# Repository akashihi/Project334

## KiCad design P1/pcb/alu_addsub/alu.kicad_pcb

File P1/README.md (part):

# P1 - Processor One 

Simple 8-bit stack based CPU built with standard logic ICs.

## Contents

- [Project organization](#project-organization)
- [Architecture](#architecture)
- [Toolchain](#toolchain)
- [Logical design]
- [Schematics and PCB]
- [Authors]
- [License]

## Project Organization

* `benchmark` - Host system benchmark code. Implements several matrix operation on 8-bit
unsigned integers.
* `docs` - More detailed documentation on the CPU design and Instruction Set Architecture.
* `prgs` - Programs written for P1 CPU using P1 mnemonics
* `tb` - Test vector generators for ALU and branching unit. 
* `tests` - Test programs in P1 mnemonics that execute every single possible opcode in a predictable manner
* `tooling` - Mnemonics translation tool `p1asm` and CPU emulator `p1emu`

CPU logical design is done in [Logisim Evolution](https://github.com/logisim-evolution/logisim-evolution), the main circuit is 
stored in `P1.circ` file. 

CPU physical design is done in [KiCad](https://www.kicad.org/)

Tooling is written in [Rust](https://rustup.rs/)

## Architecture

P1 is a simple 8-bit, stack based CPU with 8-bit address and data buses. The main characteristic of it as it is a 
stack-based CPU, meaning that all operations are executed on a hardware stack, not on addressable registers.

CPU provides four items stack with registers `X`,`Y`,`Z` and `T`, plus a "previous X value" register `X0`. 
All operations are applied to the values of registers `X` and `Y` and operations results are stored back to register `X`. 
CPU provides wide set of stack specific operations.

For an intermediate data storage CPU provides 15 addressable registers, which can be used as a temporary data storage. 
Those registers can not be used in any other operation, except reading or updating their value. However, those 
registers could be used with branching instructions, procedure calls or data accesses as the source of address, 
thus allowing indirect operations. Some of those registers will automatically increase of decrease their values upon 
indirect call, thus allowing automatic sequential reads/write of memory.

Speaking of memory, CPU support 256 bytes of RAM **and** 256 bytes of program ROM. Program memory and data memory are in 
different address spaces, however they share the same address and data buses.

More details on the CPU instructions and behaviour details can be obtained from the [Instruction Set Architecture documentation](/docs/ISA.md).

## Toolchain

What toolchain? There is no real toolchain, but rather a couple of tools that help you write and debug programs for P1 cpu.

### p1asm

Located under `tooling\p1asm` is a Rust tool to convert a program written in P1 autocode to the executable binary. `p1asm` tool
 accepts a text source file and generates a binary file, replacing source file's extension with `p1b`. Example:

````shell
>cargo run hello_world.p1s
Converting hello_world.p1s input file to "hello_world.p1b" output binary
LUP 248 -> 01001111
PUP 248 -> 01011000
WVR R15 -> 11011111
LUP 72 -> 01000100
PUP 72 -> 01011000
ST R15 -> 10011111
LUP 105 -> 01000110
PUP 105 -> 01011001
ST R15 -> 10011111
SET 32 -> 00100000
ST R15 -> 10011111
LUP 116 -> 01000111
PUP 116 -> 01010100
ST R15 -> 10011111
LUP 104 -> 01000110
PUP 104 -> 01011000
ST R15 -> 10011111
LUP 101 -> 01000110
PUP 101 -> 01010101
ST R15 -> 10011111
LUP 114 -> 01000111
PUP 114 -> 01010010
ST R15 -> 10011111
LUP 101 -> 01000110
PUP 101 -> 01010101
ST R15 -> 10011111                                                                                                                                                                                                                                                                                                          
````

`p1asm` expects an input file with a single opcode per line. For the register addressing opcodes, like `ST` please use an `R` prefix: `ST R15`.
For the register addressing opcodes, that operate on the `Y` register, please provide the register name directly: `LD Y`.

Assembly tool automatically checks that your program contains not more than 256 program steps and will fail on program memory overflow. 
Please pay attention, that you should use `SET` opcode instead of the `LUP/PUP` and `load immediate`. Assembly tool will automatically
convert those set call to either pair of `LUP/PUP` or to the short load of the immediate.

Unfortunately otherwise the tool is pretty limited and doesn't provide neither linking nor other automation. It is recommended to use supplied
`prgs\template.p1s` for tracking the addresses and track the content of the stack manually, like it is done in `tests\test_alu_ops.p1s`.

### p1emu

Second tool is located under `tooling\p1emu` and emulates the instruction set architecture of the P1 CPU. For the more precise cycle-perfect simulation
one can use the [logical design simulation](#logical-design) with logisim.

However, neither hardware implementation nor logisim provide convenient debug interface and ease of use. On the other hand the `p1emu` tool 
provides you with a simple way to run a P1 software on the host system and dumps the CPU state on each opcode processed. Additionally, 
it allows you to load pre-saved RAM or store it to the file at the end of the execution. The `p1emu` tool treats the NOP opcode as the execution
completion marker, unlike logisim model (and, obviously, hardware), which just skips to the next opcode. Example:

````shell
>cargo run hello_world.p1b -w hello_world.ram
Loading program code from hello_world.p1b
Loaded 26 bytes
PC: 000, X0: 000, X: 000, Y: 000, Z: 000, T: 000, S0: 000, S1: 000, S2: 000, S3: 000
R1: 000 R2: 000 R3: 000 R4: 000 R5: 000 R6: 000 R7: 000 R8: 000 R9: 000 R10: 000 R11: 000 R12: 000 R13: 000 R14: 000 R15: 000 
Output: 000 000 000 000 000 000 000 000 000 000  : 
Opcode: 01001111, Instruction: LUP 240
PC: 001, X0: 000, X: 240, Y: 000, Z: 000, T: 000, S0: 000, S1: 000, S2: 000, S3: 000
R1: 000 R2: 000 R3: 000 R4: 000 R5: 000 R6: 000 R7: 000 R8: 000 R9: 000 R10: 000 R11: 000 R12: 000 R13: 000 R14: 000 R15: 000 
Output: 000 000 000 000 000 000 000 000 000 000  : 
Opcode: 01011000, Instruction: PUP 8
PC: 002, X0: 000, X: 248, Y: 000, Z: 000, T: 000, S0: 000, S1: 000, S2: 000, S3: 000
R1: 000 R2: 000 R3: 000 R4: 000 R5: 000 R6: 000 R7: 000 R8: 000 R9: 000 R10: 000 R11: 000 R12: 000 R13: 000 R14: 000 R15: 000 
Output: 000 000 000 000 000 000 000 000 000 000  : 
Opcode: 11011111, Instruction: WVR 15
PC: 003, X0: 000, X: 248, Y: 000, Z: 000, T: 000, S0: 000, S1: 000, S2: 000, S3: 000
R1: 000 R2: 000 R3: 000 R4: 000 R5: 000 R6: 000 R7: 000 R8: 000 R9: 000 R10: 000 R11: 000 R12: 000 R13: 000 R14: 000 R15: 248 
Output: 000 000 000 000 000 000 000 000 000 000  : 
Opcode: 01000100, Instruction: LUP 64
PC: 004, X0: 000, X: 072, Y: 000, Z: 000, T: 000, S0: 000, S1: 000, S2: 000, S3: 000
R1: 000 R2: 000 R3: 000 R4: 000 R5: 000 R6: 000 R7: 000 R8: 000 R9: 000 R10: 000 R11: 000 R12: 000 R13: 000 R14: 000 R15: 248 
Output: 000 000 000 000 000 000 000 000 000 000  : 
Opcode: 01011000, Instruction: PUP 8
PC: 005, X0: 000, X: 072, Y: 000, Z: 000, T: 000, S0: 000, S1: 000, S2: 000, S3: 000
R1: 000 R2: 000 R3: 000 R4: 000 R5: 000 R6: 000 R7: 000 R8: 000 R9: 000 R10: 000 R11: 000 R12: 000 R13: 000 R14: 000 R15: 248 
Output: 000 000 000 000 000 000 000 000 000 000  : 
Opcode: 10011111, Instruction: ST 15
PC: 006, X0: 000, X: 072, Y: 000, Z: 000, T: 000, S0: 000, S1: 000, S2: 000, S3: 000
R1: 000 R2: 000 R3: 000 R4: 000 R5: 000 R6: 000 R7: 000 R8: 000 R9: 000 R10: 000 R11: 000 R12: 000 R13: 000 R14: 000 R15: 249 
Output: 000 000 072 000 000 000 000 000 000 000  : 
Opcode: 01000110, Instruction: LUP 96
PC: 007, X0: 000, X: 104, Y: 000, Z: 000, T: 000, S0: 000, S1: 000, S2: 000, S3: 000
R1: 000 R2: 000 R3: 000 R4: 000 R5: 000 R6: 000 R7: 000 R8: 000 R9: 000 R10: 000 R11: 000 R12: 000 R13: 000 R14: 000 R15: 249 
Output: 000 000 072 000 000 000 000 000 000 000  : 
Opcode: 01011001, Instruction: PUP 9
PC: 008, X0: 000, X: 105, Y: 000, Z: 000, T: 000, S0: 000, S1: 000, S2: 000, S3: 000
R1: 000 R2: 000 R3: 000 R4: 000 R5: 000 R6: 000 R7: 000 R8: 000 R9: 000 R10: 000 R11: 000 R12: 000 R13: 000 R14: 000 R15: 249 
Output: 000 000 072 000 000 000 000 000 000 000  : 
Opcode: 10011111, Instruction: ST 15
PC: 009, X0: 000, X: 105, Y: 000, Z: 000, T: 000, S0: 000, S1: 000, S2: 000, S3: 000
R1: 000 R2: 000 R3: 000 R4: 000 R5: 000 R6: 000 R7: 000 R8: 000 R9: 000 R10: 000 R11: 000 R12: 000 R13: 000 R14: 000 R15: 250 
Output: 000 000 072 105 000 000 000 000 000 000  : 
Opcode: 00100000, Instruction: Immediate: 32
PC: 010, X0: 000, X: 032, Y: 000, Z: 000, T: 000, S0: 000, S1: 000, S2: 000, S3: 000
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
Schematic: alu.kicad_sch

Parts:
C1, C2, C3, C4, C5, C6, C7, C8, C9, C10, C13, C14, C23, C24, C25, C26: 100n; C_1206_3216Metric
J1: 650473-5; TE_650473-5; PARTREV S
U1, U4, U6, U9, U14, U15: 74HC86; TSSOP-14_4.4x5mm_P0.65mm
U2, U5, U7: 74LS08; TSSOP-14_4.4x5mm_P0.65mm
U3, U30: 74LS32; TSSOP-14_4.4x5mm_P0.65mm
U8: 74LS32
U10: 74LS08
U13: 74LS541; SOIC-20W_7.5x12.8mm_P1.27mm
U29: 74HC238; TSSOP-16_4.4x5mm_P0.65mm
U31: 74LS621; SOIC-20W_7.5x12.8mm_P1.27mm

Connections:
+5V: C1.1, C2.1, C3.1, C4.1, C5.1, C6.1, C7.1, C8.1, C9.1, C10.1, C13.1, C14.1, C23.1, C24.1, C25.1, C26.1, J1.A32, J1.C29, J1.C32, U1.14 (VCC), U2.14 (VCC), U3.14 (VCC), U4.14 (VCC), U5.14 (VCC), U6.14 (VCC), U7.14 (VCC), U8.14 (VCC), U9.14 (VCC), U10.14 (VCC), U13.20 (VCC), U14.14 (VCC), U15.14 (VCC), U29.16 (VCC), U30.14 (VCC), U31.19 (~GBA), U31.20 (VCC)
/RESULT0: U1.3, U31.2 (A0)
/RESULT1: U1.6, U31.3 (A1)
/RESULT2: U1.8, U31.4 (A2)
/RESULT3: U1.11, U31.5 (A3)
/RESULT4: U6.3, U31.6 (A4)
/RESULT5: U6.6, U31.7 (A5)
/RESULT6: U6.8, U31.8 (A6)
/RESULT7: U6.11, U31.9 (A7)
/T0: U2.5, U4.2, U15.3
/T1: U2.13, U4.5, U15.6
/T2: U4.10, U5.5, U15.8
/T3: U4.13, U5.13, U15.11
/T4: U7.5, U9.13, U14.3
/T5: U7.13, U9.10, U14.6
/T6: U9.5, U10.5, U14.8
/T7: U9.2, U14.11
/X_IN0: J1.A19, U31.18 (B0)
/X_IN1: J1.A20, U31.17 (B1)
/X_IN2: J1.A21, U31.16 (B2)
/X_IN3: J1.A22, U31.15 (B3)
/X_IN4: J1.A23, U31.14 (B4)
/X_IN5: J1.A24, U31.13 (B5)
/X_IN6: J1.A25, U31.12 (B6)
/X_IN7: J1.A26, U31.11 (B7)
/X_OUT0: U2.4, U4.1, U13.11 (Y7)
/X_OUT1: U2.12, U4.4, U13.12 (Y6)
/X_OUT2: U4.9, U5.4, U13.13 (Y5)
/X_OUT3: U4.12, U5.12, U13.14 (Y4)
/X_OUT4: U7.4, U9.12, U13.15 (Y3)
/X_OUT5: U7.12, U9.9, U13.16 (Y2)
/X_OUT6: U9.4, U10.4, U13.17 (Y1)
/X_OUT7: U9.1, U13.18 (Y0)
/Y_OUT0: J1.A10, U15.1
/Y_OUT1: J1.A11, U15.4
/Y_OUT2: J1.A12, U15.9
/Y_OUT3: J1.A13, U15.12
/Y_OUT4: J1.A14, U14.1
/Y_OUT5: J1.A15, U14.4
/Y_OUT6: J1.A16, U14.9
/Y_OUT7: J1.A17, U14.12
GND: C1.2, C2.2, C3.2, C4.2, C5.2, C6.2, C7.2, C8.2, C9.2, C10.2, C13.2, C14.2, C23.2, C24.2, C25.2, C26.2, J1.A9, J1.A18, J1.A27, J1.B6, J1.B15, J1.B24, J1.C5, J1.C10, J1.C17, J1.C26, J1.C28, J1.C30, U1.7 (GND), U2.7 (GND), U3.7 (GND), U4.7 (GND), U5.7 (GND), U6.7 (GND), U7.7 (GND), U8.7 (GND), U8.12, U8.13, U9.7 (GND), U10.7 (GND), U10.9, U10.10, U10.12, U10.13, U13.1 (G1), U13.10 (GND), U13.19 (G2), U14.7 (GND), U15.7 (GND), U29.4 (~E1), U29.5 (~E2), U29.8 (GND), U30.4, U30.5, U30.7 (GND), U30.9, U30.10, U30.12, U30.13, U31.10 (GND)
unnamed: U1.1, U2.2, U4.3
unnamed: U1.4, U2.10, U4.6
unnamed: U1.5, U2.9, U3.3
unnamed: U1.9, U4.8, U5.2
unnamed: U1.10, U3.6, U5.1
unnamed: U1.12, U4.11, U5.10
unnamed: U1.13, U3.8, U5.9
unnamed: U2.3, U3.1
unnamed: U2.6, U3.2
unnamed: U2.8, U3.4
unnamed: U2.11, U3.5
unnamed: U3.9, U5.3
unnamed: U3.10, U5.6
unnamed: U3.11, U6.2, U7.1
unnamed: U3.12, U5.8
unnamed: U3.13, U5.11
unnamed: U6.1, U7.2, U9.11
unnamed: U6.4, U7.10, U9.8
unnamed: U6.5, U7.9, U8.3
unnamed: U6.12, U9.3
unnamed: U6.13, U8.8
unnamed: U7.3, U8.1
unnamed: U7.6, U8.2
unnamed: U7.8, U8.4
unnamed: U7.11, U8.5
unnamed: U6.10, U8.6, U10.1
unnamed: U6.9, U9.6, U10.2
unnamed: U8.9, U10.3
unnamed: U8.10, U10.6
unnamed: J1.A8, U13.2 (A0)
unnamed: J1.A7, U13.3 (A1)
unnamed: J1.A6, U13.4 (A2)
unnamed: J1.A5, U13.5 (A3)
unnamed: J1.A4, U13.6 (A4)
unnamed: J1.A3, U13.7 (A5)
unnamed: J1.A2, U13.8 (A6)
unnamed: J1.A1, U13.9 (A7)
unnamed: J1.A31, U29.1 (A0)
unnamed: J1.A30, U29.2 (A1)
unnamed: J1.A29, U29.3 (A2)
unnamed: J1.A28, U29.6 (E3)
unnamed: U29.15 (Y0), U30.1
unnamed: U1.2, U2.1, U14.2, U14.5, U14.10, U14.13, U15.2, U15.5, U15.10, U15.13, U29.14 (Y1), U30.2
unnamed: U30.3, U31.1 (GAB)

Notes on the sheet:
Subtractor XORs decoupling
A0/B0 Adder
A7/B7 Adder
4-bit adder decoupling
A1/B1 Adder
2's complement
A5/B5 Adder
A6/B6 Adder
A2/B2 Adder
A3/B3 Adder
A4/B4 Adder

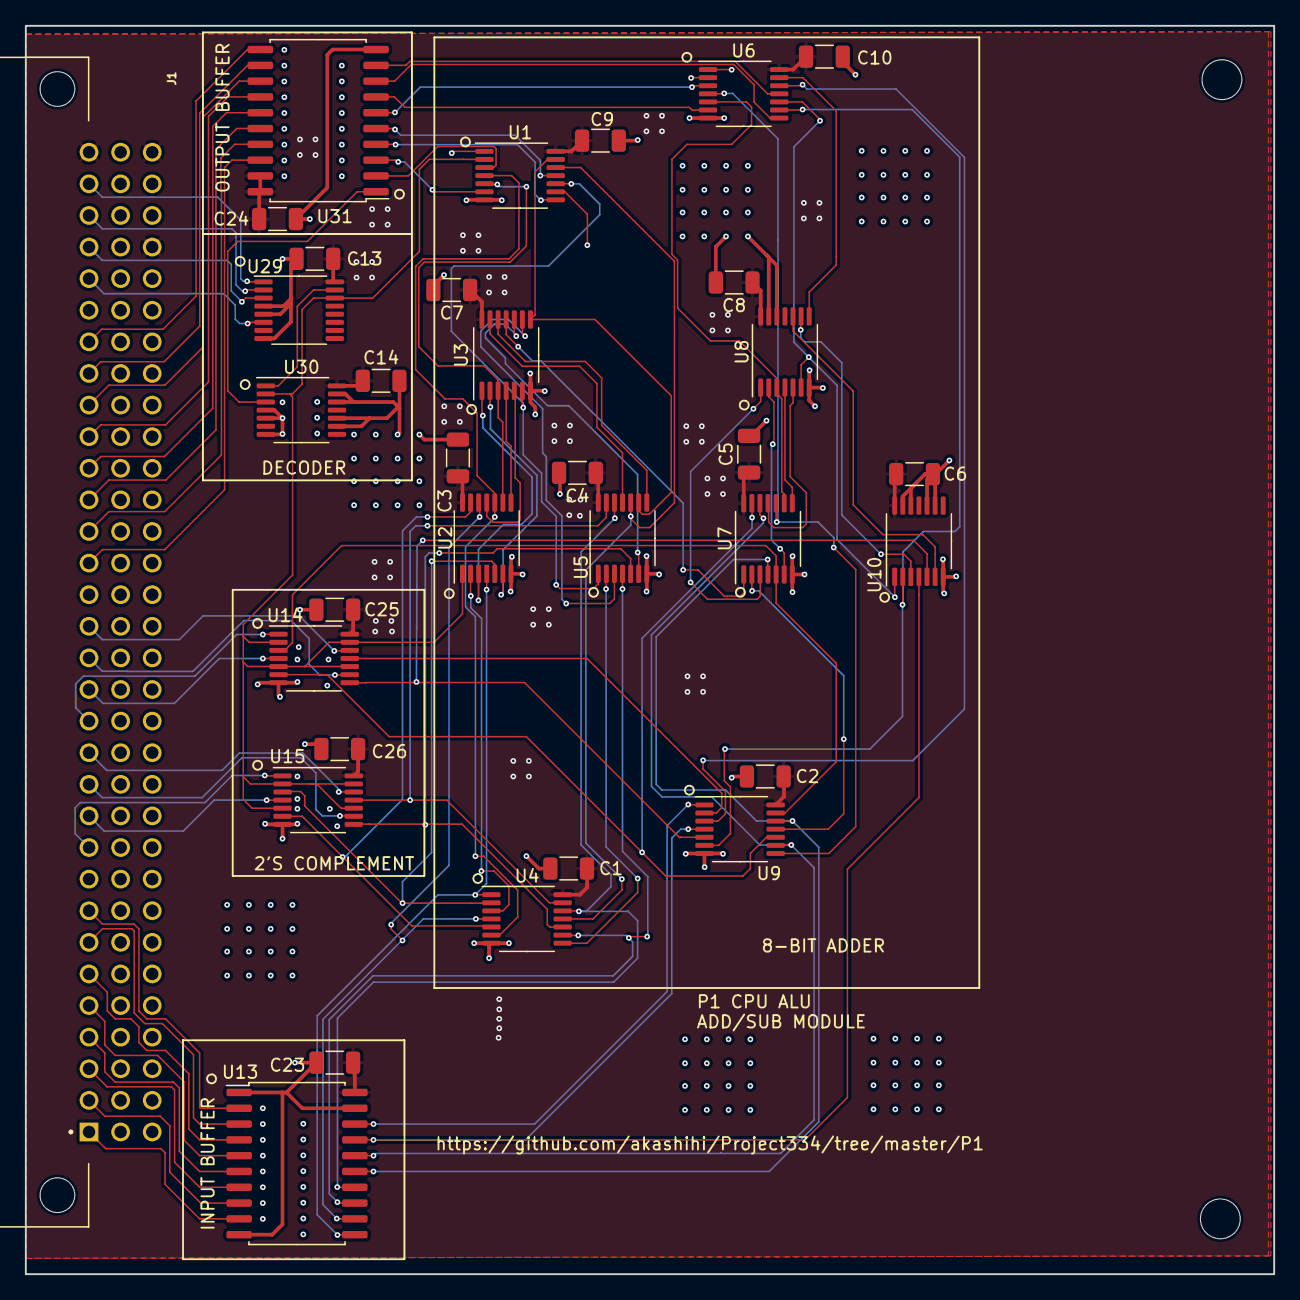
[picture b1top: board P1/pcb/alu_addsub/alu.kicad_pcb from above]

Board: 4 copper layers, 100.3 x 100.3 mm, 33 parts (0 on the bottom side), 86 nets.

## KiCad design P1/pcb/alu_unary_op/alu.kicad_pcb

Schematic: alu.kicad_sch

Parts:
C1, C23, C24, C25, C26, C27, C28, C29, C30: 100n; C_1206_3216Metric
J1: 650473-5; TE_650473-5; PARTREV S
U13: 74LS541; SOIC-20W_7.5x12.8mm_P1.27mm
U23, U24: 74HC04; TSSOP-14_4.4x5mm_P0.65mm
U25, U28: 74LS621; SOIC-20W_7.5x12.8mm_P1.27mm
U26, U27: 74LS157; TSSOP-16_4.4x5mm_P0.65mm
U29: 74HC238; TSSOP-16_4.4x5mm_P0.65mm
U30: 74LS32; TSSOP-14_4.4x5mm_P0.65mm

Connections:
+5V: C1.1, C23.1, C24.1, C25.1, C26.1, C27.1, C28.1, C29.1, C30.1, J1.A32, J1.C29, J1.C32, U13.20 (VCC), U23.14 (VCC), U24.5, U24.9, U24.11, U24.13, U24.14 (VCC), U25.19 (~GBA), U25.20 (VCC), U26.16 (VCC), U27.16 (VCC), U28.19 (~GBA), U28.20 (VCC), U29.16 (VCC), U30.14 (VCC)
/X_IN0: J1.A19, U25.18 (B0), U28.18 (B0)
/X_IN1: J1.A20, U25.17 (B1), U28.17 (B1)
/X_IN2: J1.A21, U25.16 (B2), U28.16 (B2)
/X_IN3: J1.A22, U25.15 (B3), U28.15 (B3)
/X_IN4: J1.A23, U25.14 (B4), U28.14 (B4)
/X_IN5: J1.A24, U25.13 (B5), U28.13 (B5)
/X_IN6: J1.A25, U25.12 (B6), U28.12 (B6)
/X_IN7: J1.A26, U25.11 (B7), U28.11 (B7)
/X_OUT0: U13.11 (Y7), U23.5, U26.6 (I1b)
/X_OUT1: U13.12 (Y6), U23.3, U26.2 (I0a), U26.10 (I1c)
/X_OUT2: U13.13 (Y5), U23.1, U26.5 (I0b), U26.13 (I1d)
/X_OUT3: U13.14 (Y4), U23.9, U26.11 (I0c), U27.3 (I1a)
/X_OUT4: U13.15 (Y3), U23.11, U26.14 (I0d), U27.6 (I1b)
/X_OUT5: U13.16 (Y2), U23.13, U27.2 (I0a), U27.10 (I1c)
/X_OUT6: U13.17 (Y1), U24.3, U27.5 (I0b), U27.13 (I1d)
/X_OUT7: U13.18 (Y0), U24.1, U27.11 (I0c)
GND: C1.2, C23.2, C24.2, C25.2, C26.2, C27.2, C28.2, C29.2, C30.2, J1.A9, J1.A18, J1.A27, J1.B6, J1.B15, J1.B24, J1.C5, J1.C10, J1.C17, J1.C26, J1.C28, J1.C30, U13.1 (G1), U13.10 (GND), U13.19 (G2), U23.7 (GND), U24.7 (GND), U25.10 (GND), U26.3 (I1a), U26.8 (GND), U26.15 (E), U27.8 (GND), U27.14 (I0d), U27.15 (E), U28.10 (GND), U29.4 (~E1), U29.5 (~E2), U29.8 (GND), U30.1, U30.2, U30.7 (GND), U30.9, U30.10, U30.12, U30.13
unnamed: J1.A8, U13.2 (A0)
unnamed: J1.A7, U13.3 (A1)
unnamed: J1.A6, U13.4 (A2)
unnamed: J1.A5, U13.5 (A3)
unnamed: J1.A4, U13.6 (A4)
unnamed: J1.A3, U13.7 (A5)
unnamed: J1.A2, U13.8 (A6)
unnamed: J1.A1, U13.9 (A7)
unnamed: U23.6, U25.2 (A0)
unnamed: U23.4, U25.3 (A1)
unnamed: U23.2, U25.4 (A2)
unnamed: U23.8, U25.5 (A3)
unnamed: U23.10, U25.6 (A4)
unnamed: U23.12, U25.7 (A5)
unnamed: U24.4, U25.8 (A6)
unnamed: U24.2, U25.9 (A7)
unnamed: U25.1 (GAB), U29.10 (Y5)
unnamed: U26.1 (S), U27.1 (S), U29.13 (Y2), U30.4
unnamed: U26.4 (Za), U28.2 (A0)
unnamed: U26.7 (Zb), U28.3 (A1)
unnamed: U26.9 (Zc), U28.4 (A2)
unnamed: U26.12 (Zd), U28.5 (A3)
unnamed: U27.4 (Za), U28.6 (A4)
unnamed: U27.7 (Zb), U28.7 (A5)
unnamed: U27.9 (Zc), U28.8 (A6)
unnamed: U27.12 (Zd), U28.9 (A7)
unnamed: U28.1 (GAB), U30.6
unnamed: J1.A31, U29.1 (A0)
unnamed: J1.A30, U29.2 (A1)
unnamed: J1.A29, U29.3 (A2)
unnamed: J1.A28, U29.6 (E3)
unnamed: U29.12 (Y3), U30.5

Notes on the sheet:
L/R SHIFT OP
NOT OP

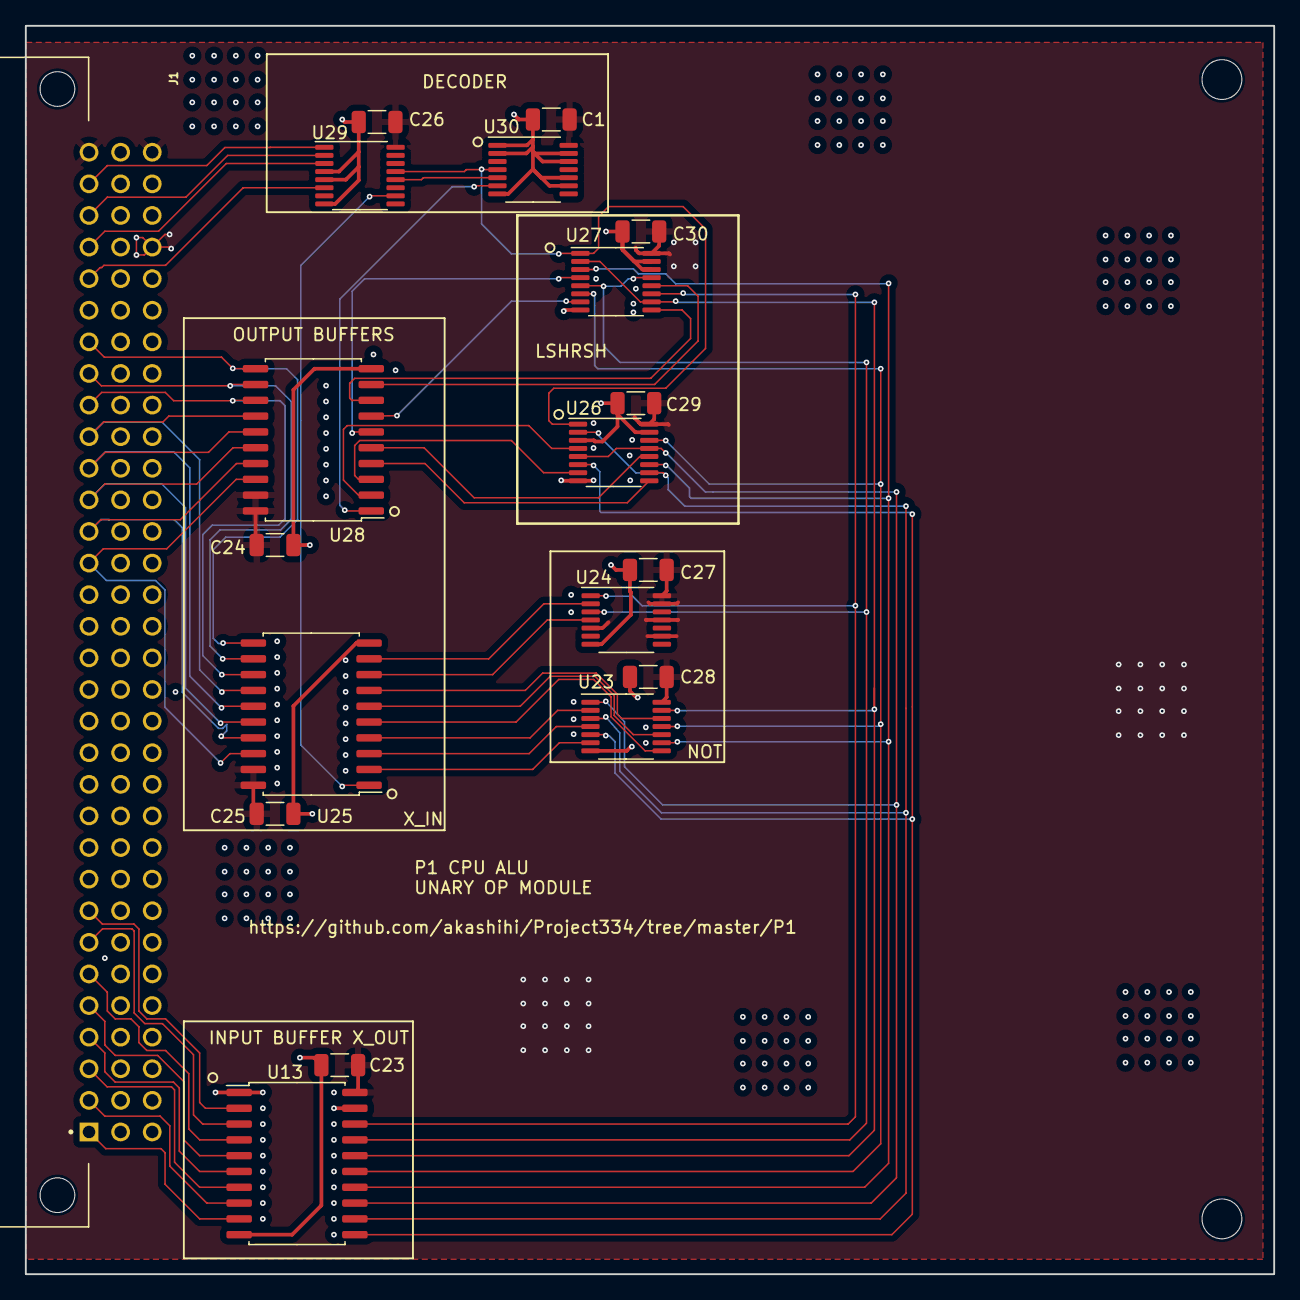
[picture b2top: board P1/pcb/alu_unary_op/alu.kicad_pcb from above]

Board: 4 copper layers, 100.3 x 100.3 mm, 19 parts (0 on the bottom side), 50 nets.

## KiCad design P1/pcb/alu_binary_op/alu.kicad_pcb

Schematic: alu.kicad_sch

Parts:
C13, C14, C15, C23, C24, C25, C26, C27, C28, C29, C30: 100n; C_1206_3216Metric
J1: 650473-5; TE_650473-5; PARTREV S
U13: 74LS541; SOIC-20W_7.5x12.8mm_P1.27mm
U14, U15: 74HC86; TSSOP-14_4.4x5mm_P0.65mm
U16, U19, U22: 74LS621; SOIC-20W_7.5x12.8mm_P1.27mm
U17, U18: 74LS08; TSSOP-14_4.4x5mm_P0.65mm
U20, U21: 74LS32; TSSOP-14_4.4x5mm_P0.65mm
U29: 74HC238; TSSOP-16_4.4x5mm_P0.65mm

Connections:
+5V: C13.1, C14.1, C15.1, C23.1, C24.1, C25.1, C26.1, C27.1, C28.1, C29.1, C30.1, J1.A32, J1.C29, J1.C32, U13.20 (VCC), U14.14 (VCC), U15.14 (VCC), U16.19 (~GBA), U16.20 (VCC), U17.14 (VCC), U18.14 (VCC), U19.19 (~GBA), U19.20 (VCC), U20.14 (VCC), U21.14 (VCC), U22.19 (~GBA), U22.20 (VCC), U29.16 (VCC)
/X_IN0: J1.A19, U16.18 (B0), U19.18 (B0), U22.18 (B0)
/X_IN1: J1.A20, U16.17 (B1), U19.17 (B1), U22.17 (B1)
/X_IN2: J1.A21, U16.16 (B2), U19.16 (B2), U22.16 (B2)
/X_IN3: J1.A22, U16.15 (B3), U19.15 (B3), U22.15 (B3)
/X_IN4: J1.A23, U16.14 (B4), U19.14 (B4), U22.14 (B4)
/X_IN5: J1.A24, U16.13 (B5), U19.13 (B5), U22.13 (B5)
/X_IN6: J1.A25, U16.12 (B6), U19.12 (B6), U22.12 (B6)
/X_IN7: J1.A26, U16.11 (B7), U19.11 (B7), U22.11 (B7)
/X_OUT0: U13.11 (Y7), U14.4, U17.5, U20.5
/X_OUT1: U13.12 (Y6), U14.1, U17.2, U20.2
/X_OUT2: U13.13 (Y5), U14.9, U17.10, U20.10
/X_OUT3: U13.14 (Y4), U14.12, U17.13, U20.13
/X_OUT4: U13.15 (Y3), U15.4, U18.5, U21.5
/X_OUT5: U13.16 (Y2), U15.1, U18.2, U21.2
/X_OUT6: U13.17 (Y1), U15.9, U18.10, U21.10
/X_OUT7: U13.18 (Y0), U15.12, U18.13, U21.13
/Y_OUT0: J1.A10, U14.5, U17.4, U20.4
/Y_OUT1: J1.A11, U14.2, U17.1, U20.1
/Y_OUT2: J1.A12, U14.10, U17.9, U20.9
/Y_OUT3: J1.A13, U14.13, U17.12, U20.12
/Y_OUT4: J1.A14, U15.5, U18.4, U21.4
/Y_OUT5: J1.A15, U15.2, U18.1, U21.1
/Y_OUT6: J1.A16, U15.10, U18.9, U21.9
/Y_OUT7: J1.A17, U15.13, U18.12, U21.12
GND: C13.2, C14.2, C15.2, C23.2, C24.2, C25.2, C26.2, C27.2, C28.2, C29.2, C30.2, J1.A9, J1.A18, J1.A27, J1.B6, J1.B15, J1.B24, J1.C5, J1.C10, J1.C17, J1.C26, J1.C28, J1.C30, U13.1 (G1), U13.10 (GND), U13.19 (G2), U14.7 (GND), U15.7 (GND), U16.10 (GND), U17.7 (GND), U18.7 (GND), U19.10 (GND), U20.7 (GND), U21.7 (GND), U22.10 (GND), U29.4 (~E1), U29.5 (~E2), U29.8 (GND)
unnamed: J1.A8, U13.2 (A0)
unnamed: J1.A7, U13.3 (A1)
unnamed: J1.A6, U13.4 (A2)
unnamed: J1.A5, U13.5 (A3)
unnamed: J1.A4, U13.6 (A4)
unnamed: J1.A3, U13.7 (A5)
unnamed: J1.A2, U13.8 (A6)
unnamed: J1.A1, U13.9 (A7)
unnamed: U14.6, U16.2 (A0)
unnamed: U14.3, U16.3 (A1)
unnamed: U14.8, U16.4 (A2)
unnamed: U14.11, U16.5 (A3)
unnamed: U15.6, U16.6 (A4)
unnamed: U15.3, U16.7 (A5)
unnamed: U15.8, U16.8 (A6)
unnamed: U15.11, U16.9 (A7)
unnamed: U16.1 (GAB), U29.11 (Y4)
unnamed: U17.6, U19.2 (A0)
unnamed: U17.3, U19.3 (A1)
unnamed: U17.8, U19.4 (A2)
unnamed: U17.11, U19.5 (A3)
unnamed: U18.6, U19.6 (A4)
unnamed: U18.3, U19.7 (A5)
unnamed: U18.8, U19.8 (A6)
unnamed: U18.11, U19.9 (A7)
unnamed: U19.1 (GAB), U29.9 (Y6)
unnamed: U20.6, U22.2 (A0)
unnamed: U20.3, U22.3 (A1)
unnamed: U20.8, U22.4 (A2)
unnamed: U20.11, U22.5 (A3)
unnamed: U21.6, U22.6 (A4)
unnamed: U21.3, U22.7 (A5)
unnamed: U21.8, U22.8 (A6)
unnamed: U21.11, U22.9 (A7)
unnamed: U22.1 (GAB), U29.7 (Y7)
unnamed: J1.A31, U29.1 (A0)
unnamed: J1.A30, U29.2 (A1)
unnamed: J1.A29, U29.3 (A2)
unnamed: J1.A28, U29.6 (E3)

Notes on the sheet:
OR OP
XOR OP
AND OP

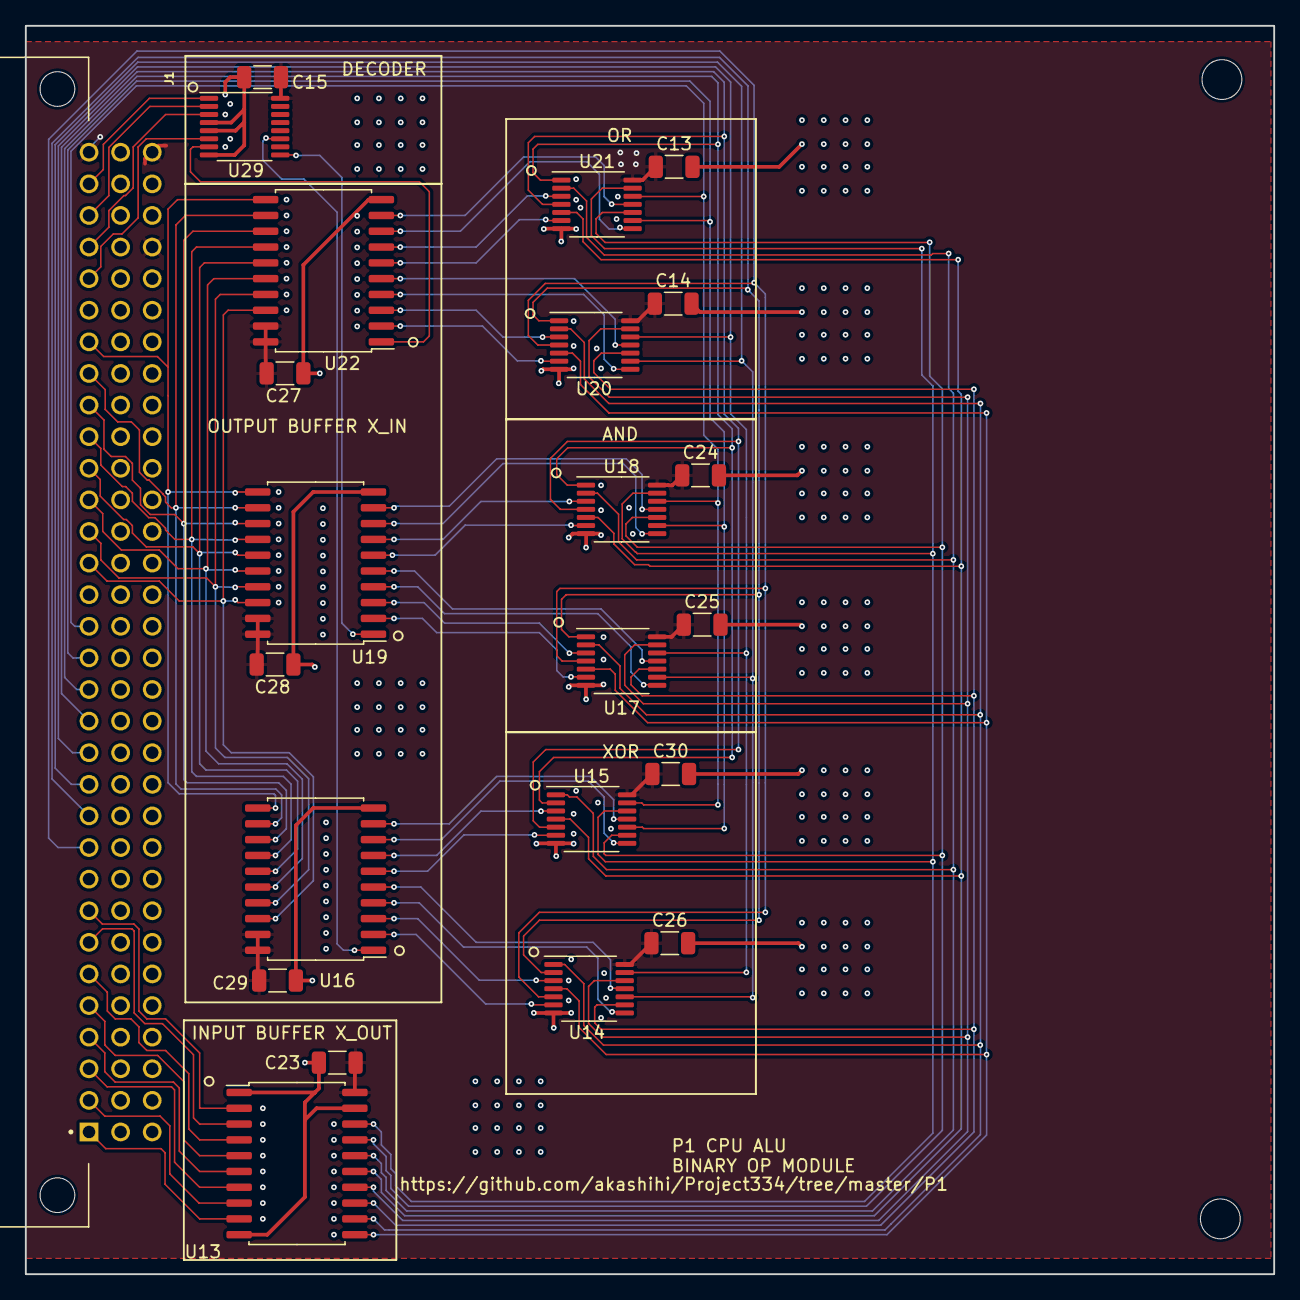
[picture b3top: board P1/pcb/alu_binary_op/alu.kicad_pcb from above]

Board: 4 copper layers, 100.3 x 100.3 mm, 23 parts (0 on the bottom side), 65 nets.

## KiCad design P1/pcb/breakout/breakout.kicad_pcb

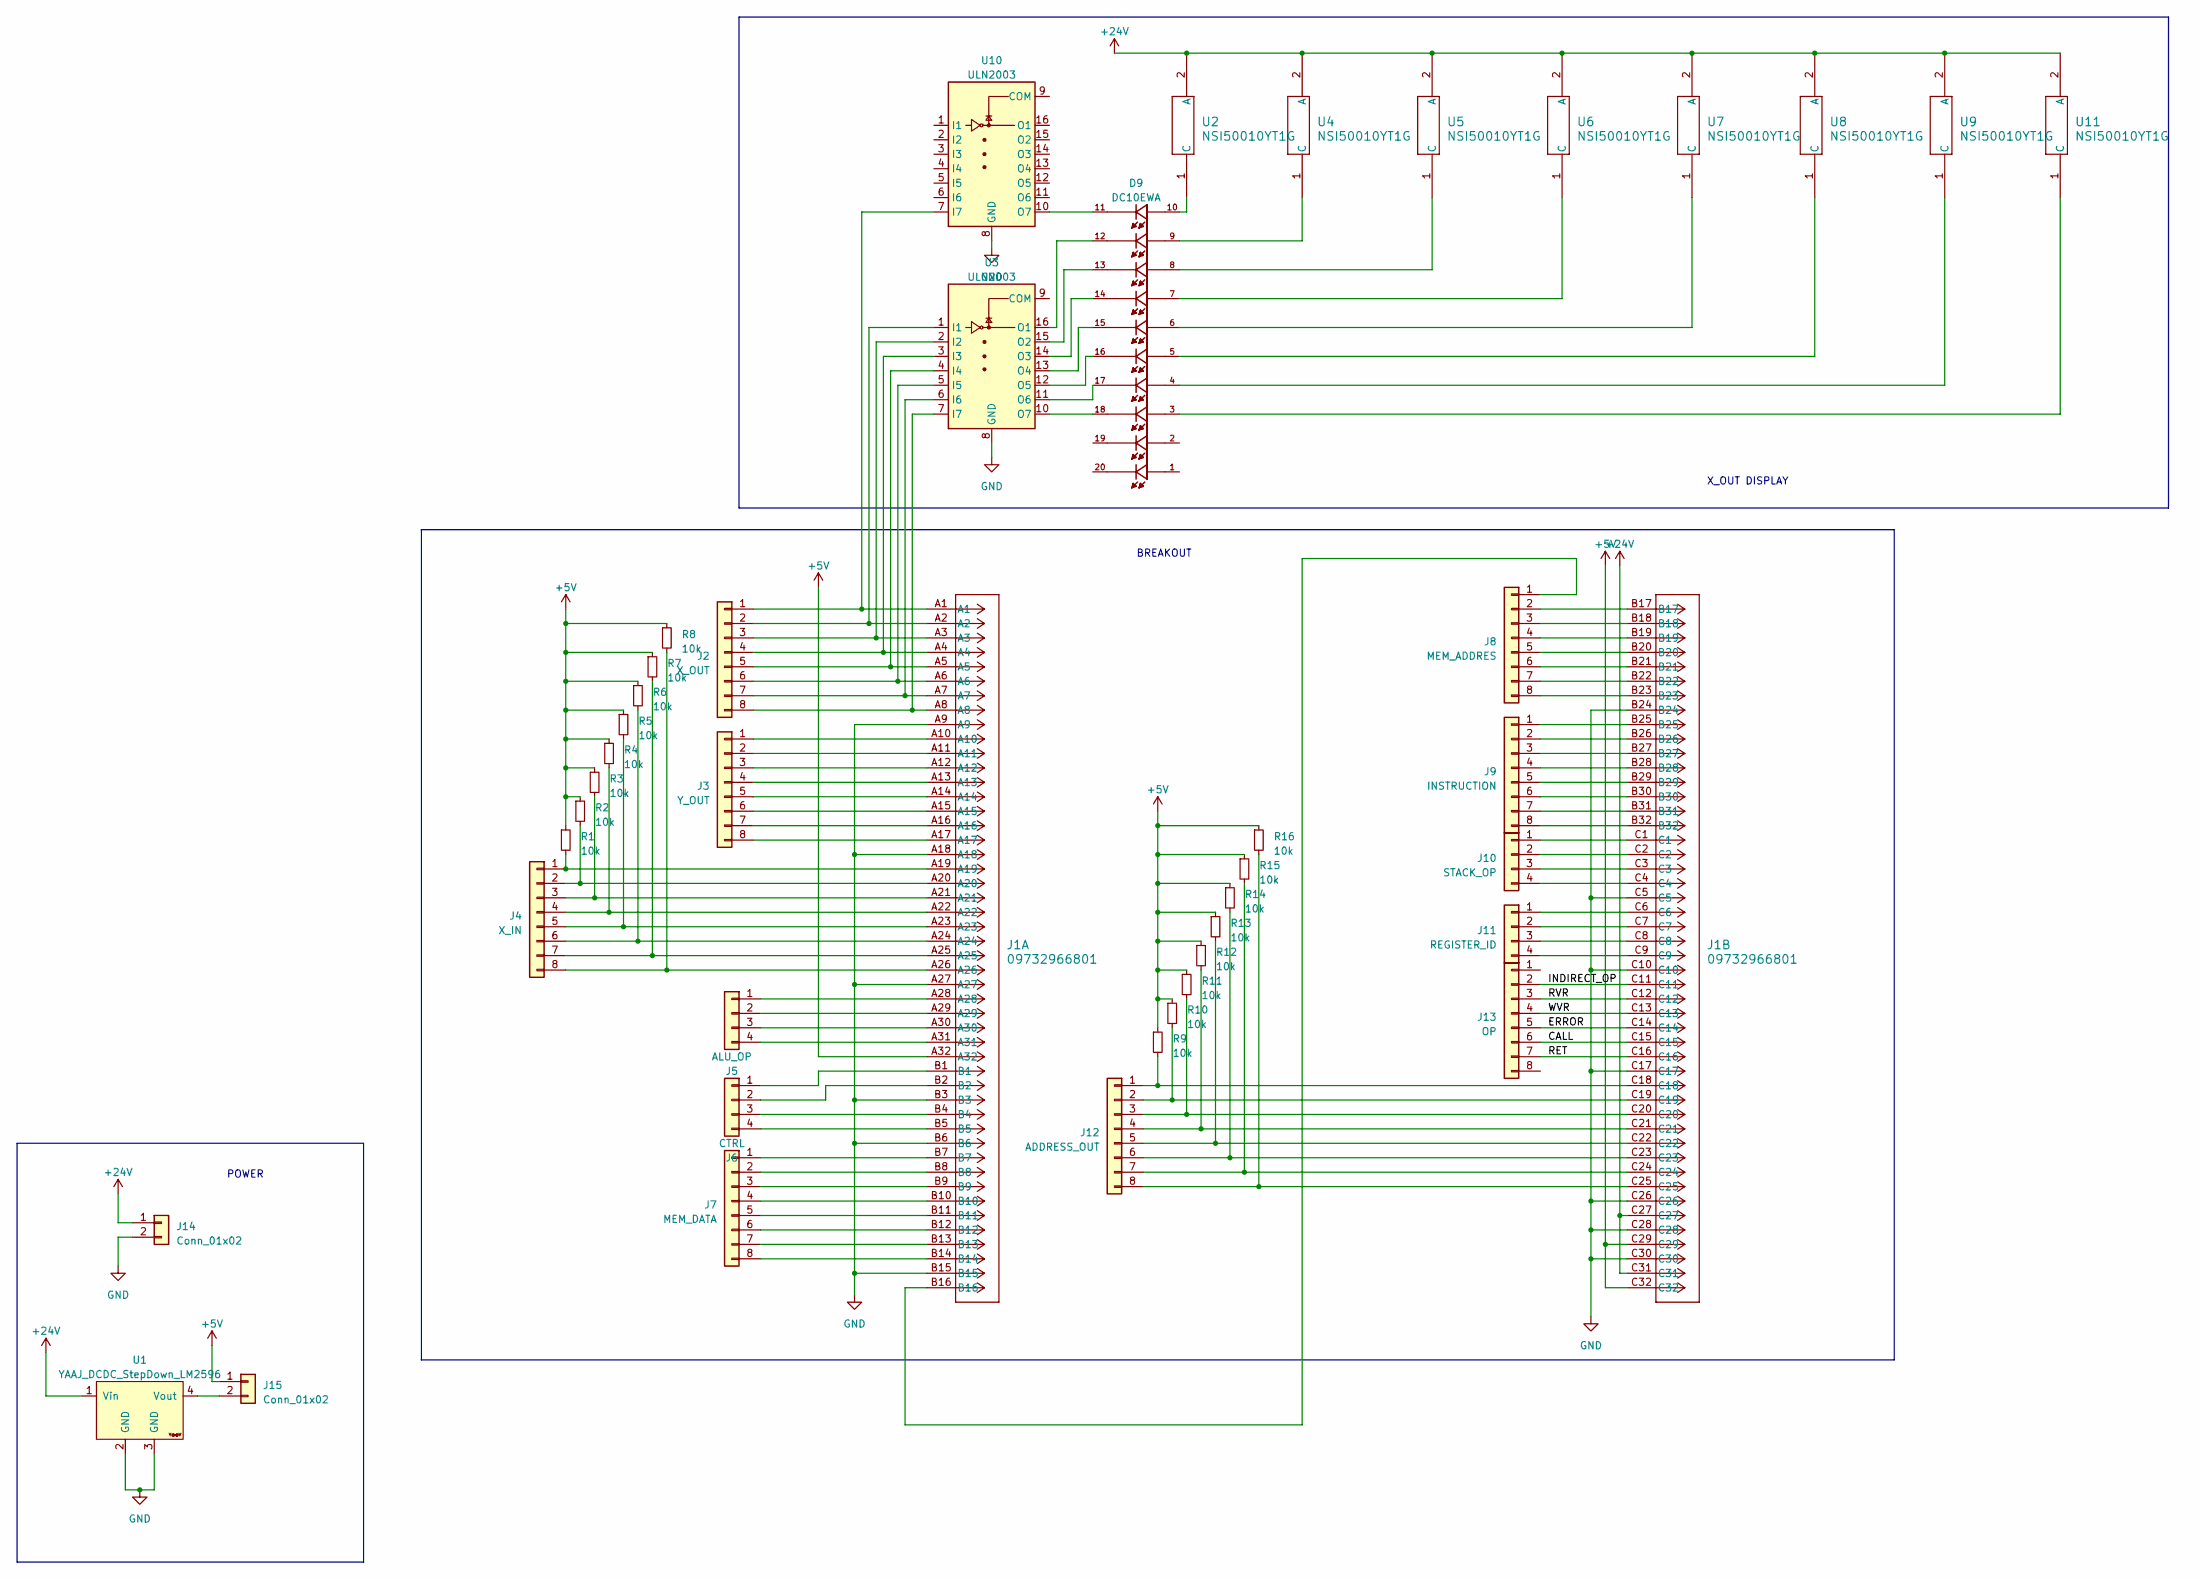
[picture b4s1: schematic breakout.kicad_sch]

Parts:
D9: DC10EWA; DIP750W50P254L2540H825Q20; PARTREV V.10A
J1: 09732966801; DIN41612_C_3x32_Female_Vertical_THT
J2: X_OUT; PinHeader_1x08_P2.54mm_Vertical
J3: Y_OUT; PinHeader_1x08_P2.54mm_Vertical
J4: X_IN; PinHeader_1x08_P2.54mm_Vertical
J5: ALU_OP; PinHeader_1x04_P2.54mm_Vertical
J6: CTRL; PinHeader_1x04_P2.54mm_Vertical
J7: MEM_DATA; PinHeader_1x08_P2.54mm_Vertical
J8: MEM_ADDRES; PinHeader_1x08_P2.54mm_Vertical
J9: INSTRUCTION; PinHeader_1x08_P2.54mm_Vertical
J10: STACK_OP; PinHeader_1x04_P2.54mm_Vertical
J11: REGISTER_ID; PinHeader_1x04_P2.54mm_Vertical
J12: ADDRESS_OUT; PinHeader_1x08_P2.54mm_Vertical
J13: OP; PinHeader_1x08_P2.54mm_Vertical
J14, J15: Conn_01x02; PinHeader_1x02_P2.54mm_Vertical
R1, R2, R3, R4, R5, R6, R7, R8, R9, R10, R11, R12, R13, R14, R15, R16: 10k; R_0805_2012Metric_Pad1.20x1.40mm_HandSolder
U1: YAAJ_DCDC_StepDown_LM2596
U2, U4, U5, U6, U7, U8, U9, U11: NSI50010YT1G; SOD123-2_ONS
U3, U10: ULN2003; TSSOP-16-1EP_4.4x5mm_P0.65mm

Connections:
+5V: J1.A32, J1.C29, J1.C32, J15.1, R1.1, R2.1, R3.1, R4.1, R5.1, R6.1, R7.1, R8.1, R9.1, R10.1, R11.1, R12.1, R13.1, R14.1, R15.1, R16.1
+24V: J1.C27, J1.C31, J14.1, U1.1 (Vin), U2.2 (A), U4.2 (A), U5.2 (A), U6.2 (A), U7.2 (A), U8.2 (A), U9.2 (A), U11.2 (A)
/CALL: J1.C15, J13.6
/ERROR: J1.C14, J13.5
/INDIRECT_OP: J1.C11, J13.2
/RET: J1.C16, J13.7
/RVR: J1.C12, J13.3
/WVR: J1.C13, J13.4
GND: J1.A9, J1.A18, J1.A27, J1.B3, J1.B6, J1.B15, J1.B24, J1.C5, J1.C10, J1.C17, J1.C26, J1.C28, J1.C30, J14.2, U1.2 (GND), U1.3 (GND), U3.8 (GND), U10.8 (GND)
unnamed: J1.A1, J2.1, U10.7 (I7)
unnamed: J1.A2, J2.2, U3.1 (I1)
unnamed: J1.A3, J2.3, U3.2 (I2)
unnamed: J1.A4, J2.4, U3.3 (I3)
unnamed: J1.A5, J2.5, U3.4 (I4)
unnamed: J1.A6, J2.6, U3.5 (I5)
unnamed: J1.A7, J2.7, U3.6 (I6)
unnamed: J1.A8, J2.8, U3.7 (I7)
unnamed: J1.A10, J3.1
unnamed: J1.A11, J3.2
unnamed: J1.A12, J3.3
unnamed: J1.A13, J3.4
unnamed: J1.A14, J3.5
unnamed: J1.A15, J3.6
unnamed: J1.A16, J3.7
unnamed: J1.A17, J3.8
unnamed: J1.A19, J4.1, R1.2
unnamed: J1.A20, J4.2, R2.2
unnamed: J1.A21, J4.3, R3.2
unnamed: J1.A22, J4.4, R4.2
unnamed: J1.A23, J4.5, R5.2
unnamed: J1.A24, J4.6, R6.2
unnamed: J1.A25, J4.7, R7.2
unnamed: J1.A26, J4.8, R8.2
unnamed: J1.A28, J5.1
unnamed: J1.A29, J5.2
unnamed: J1.A30, J5.3
unnamed: J1.A31, J5.4
unnamed: J1.B1, J6.1
unnamed: J1.B2, J6.2
unnamed: J1.B4, J6.3
unnamed: J1.B5, J6.4
unnamed: J1.B7, J7.1
unnamed: J1.B8, J7.2
unnamed: J1.B9, J7.3
unnamed: J1.B10, J7.4
unnamed: J1.B11, J7.5
unnamed: J1.B12, J7.6
unnamed: J1.B13, J7.7
unnamed: J1.B14, J7.8
unnamed: J1.B16, J8.1
unnamed: J1.B17, J8.2
unnamed: J1.B18, J8.3
unnamed: J1.B19, J8.4
unnamed: J1.B20, J8.5
unnamed: J1.B21, J8.6
unnamed: J1.B22, J8.7
unnamed: J1.B23, J8.8
unnamed: J1.B25, J9.1
unnamed: J1.B26, J9.2
unnamed: J1.B27, J9.3
unnamed: J1.B28, J9.4
unnamed: J1.B29, J9.5
unnamed: J1.B30, J9.6
unnamed: J1.B31, J9.7
unnamed: J1.B32, J9.8
unnamed: J1.C1, J10.1
unnamed: J1.C2, J10.2
unnamed: J1.C3, J10.3
unnamed: J1.C4, J10.4
unnamed: J1.C6, J11.1
unnamed: J1.C7, J11.2
unnamed: J1.C8, J11.3
unnamed: J1.C9, J11.4
unnamed: J1.C18, J12.1, R9.2
unnamed: J1.C19, J12.2, R10.2
unnamed: J1.C20, J12.3, R11.2
unnamed: J1.C21, J12.4, R12.2
unnamed: J1.C22, J12.5, R13.2
unnamed: J1.C23, J12.6, R14.2
unnamed: J1.C24, J12.7, R15.2
unnamed: J1.C25, J12.8, R16.2
unnamed: J15.2, U1.4 (Vout)
unnamed: D9.10, U2.1 (C)
unnamed: D9.12, U3.16 (O1)
unnamed: D9.13, U3.15 (O2)
unnamed: D9.14, U3.14 (O3)
unnamed: D9.15, U3.13 (O4)
unnamed: D9.16, U3.12 (O5)
unnamed: D9.17, U3.11 (O6)
unnamed: D9.18, U3.10 (O7)
unnamed: D9.9, U4.1 (C)
unnamed: D9.8, U5.1 (C)
unnamed: D9.7, U6.1 (C)
unnamed: D9.6, U7.1 (C)
unnamed: D9.5, U8.1 (C)
unnamed: D9.4, U9.1 (C)
unnamed: D9.11, U10.10 (O7)
unnamed: D9.3, U11.1 (C)

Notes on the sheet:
X_OUT DISPLAY
BREAKOUT
POWER

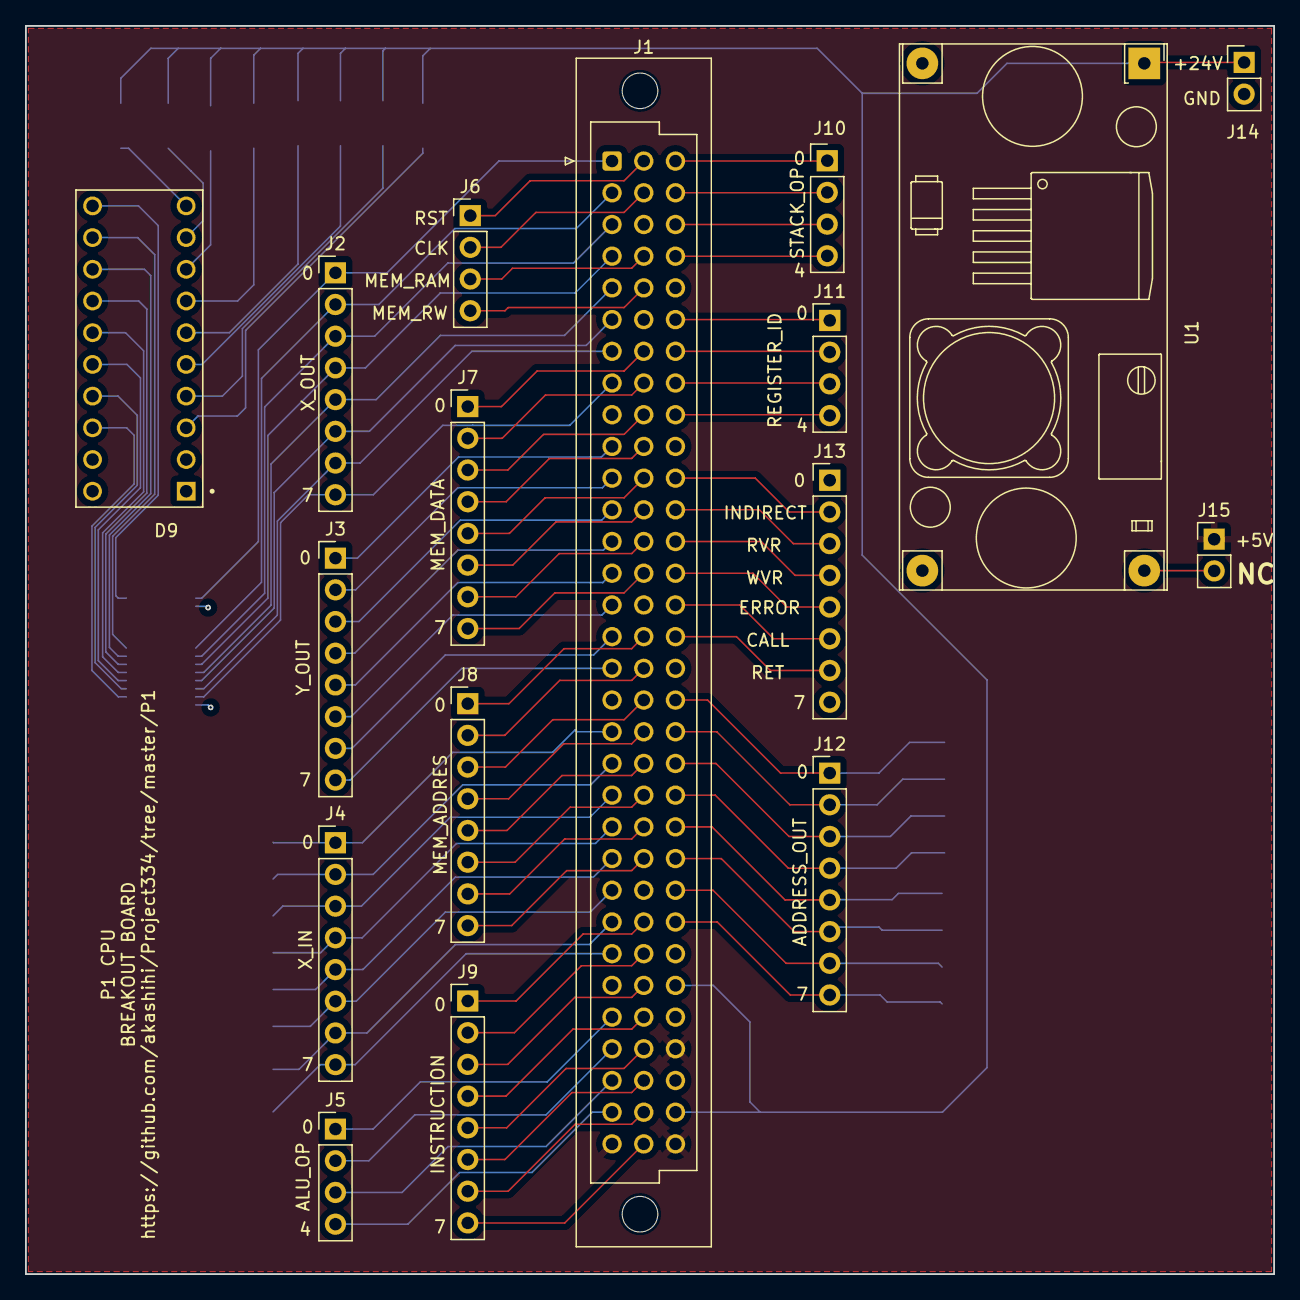
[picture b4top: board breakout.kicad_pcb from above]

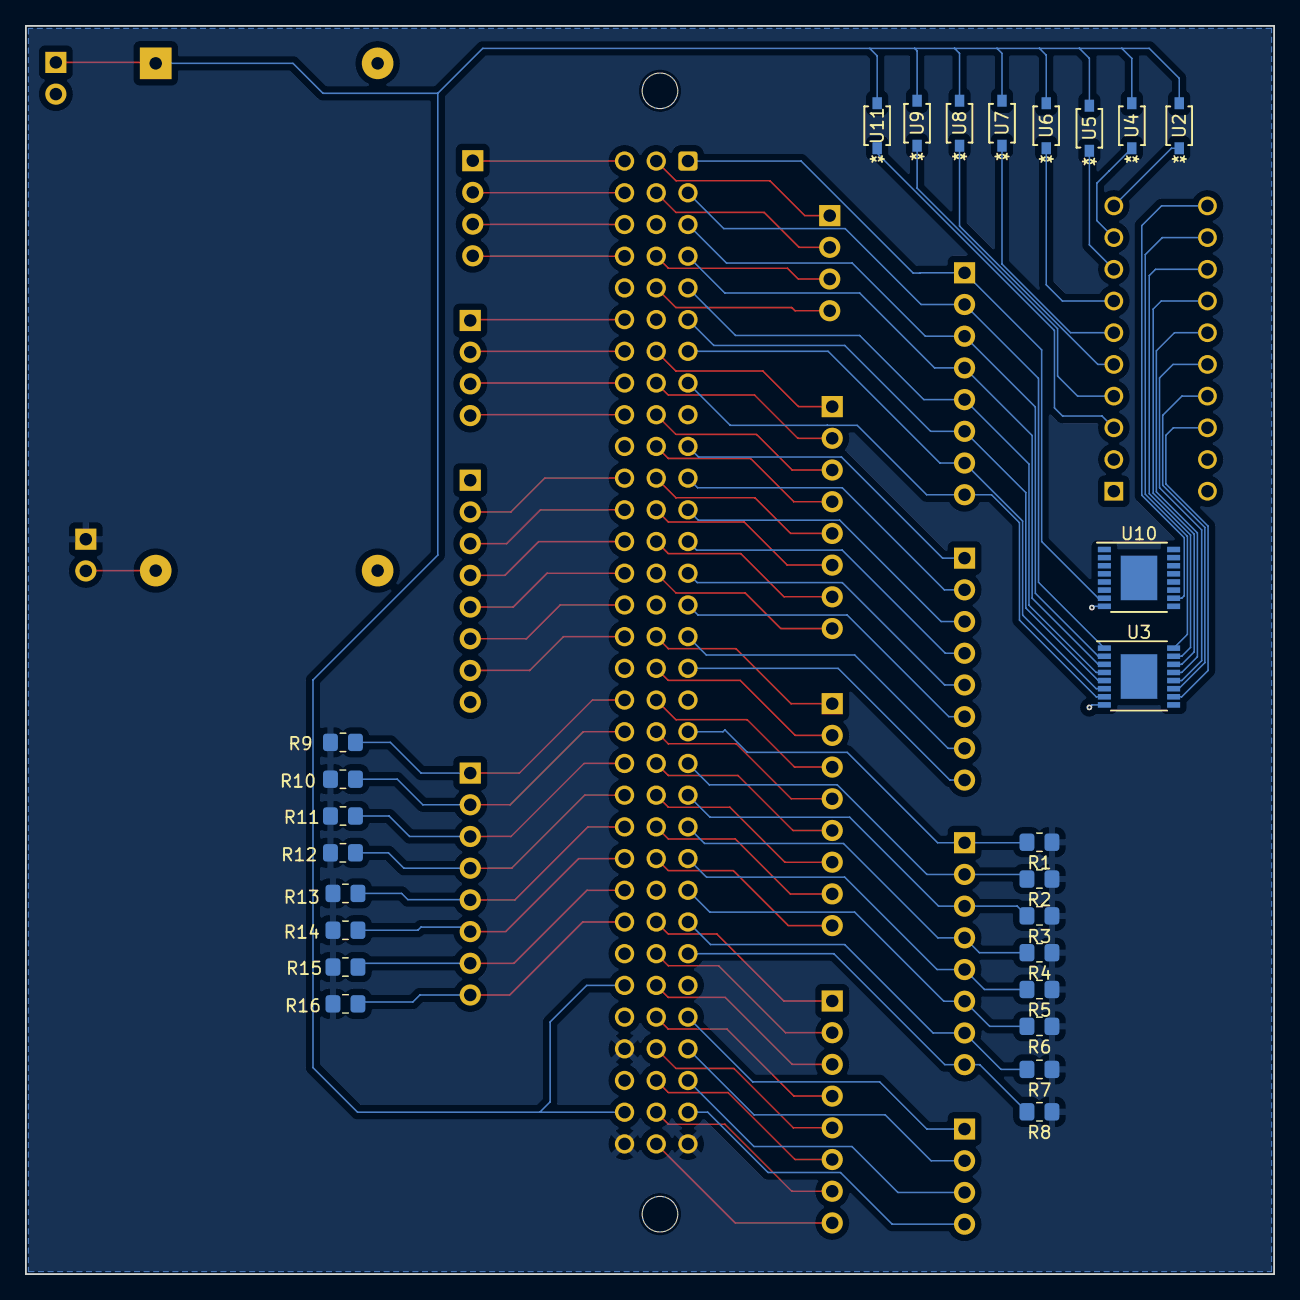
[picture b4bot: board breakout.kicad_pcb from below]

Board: 4 copper layers, 100.0 x 100.0 mm, 43 parts (26 on the bottom side), 98 nets.
